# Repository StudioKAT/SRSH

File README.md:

# SRSH

## 概要 / Overview

**SRSH** は、8Stepのシフトレジスタと、8段のサンプル＆ホールド（S&H）を組み合わせたモジュールです。  
- GATE 出力 ×8 を備えた 8Stepシフトレジスタ（DATA / XOR 入力、WRITE / DELETE ボタン付き）  
- シフトレジスタのビットの動きに連動して電圧を受け渡す8段の S&H  
- 8 つのビットを 1 本の CV にまとめる R2R 出力  
の3つを1台にまとめ、リズムとランダムな電圧を同時に作り出せます。  
S&H の入力（SOURCE）に何も挿さなければ、内蔵のホワイトノイズをサンプルします。

---

**SRSH** is a module that combines an 8-step shift register with an 8-stage sample & hold (S&H).  
- An 8-step shift register with 8 GATE outputs (with DATA / XOR inputs and WRITE / DELETE buttons)  
- An 8-stage S&H that passes voltages along in step with the movement of the shift register bits  
- An R2R output that combines the 8 bits into a single CV  

All three are combined in one module, so you can create rhythms and random voltages at the same time.  
When nothing is patched into the S&H input (SOURCE), the module samples its built-in white noise.

## 仕様 / Spec
- Format: Eurorack
- Function: 
- Current needs: +12V: 90mA, -12V: 40mA
- Width: 8 HP
- Depth: 27mm (including power connector)

## 販売 / Sales

StudioKATオフィシャルショップで販売しています。(日本国内限定)  
https://www.studiokat.jp/164466540

## ライセンス / License

この作品は [Creative Commons 表示 - 継承 4.0 国際 (CC BY-SA 4.0)](https://creativecommons.org/licenses/by-sa/4.0/deed.ja) の下でライセンスされています。  
This work is licensed under the [Creative Commons Attribution-ShareAlike 4.0 International License](https://creativecommons.org/licenses/by-sa/4.0/).

## クレジット / Credits

- Designed by : StudioKAT
- Website : https://www.studiokat.jp/
- GitHub : https://github.com/StudioKAT
- X(Twitter) : https://x.com/StudioKAT_synth
- Instagram : https://www.instagram.com/studiokat_modular/

## 更新履歴 / Changelog

- `2026-10-30` v1.0 Released version 1.0

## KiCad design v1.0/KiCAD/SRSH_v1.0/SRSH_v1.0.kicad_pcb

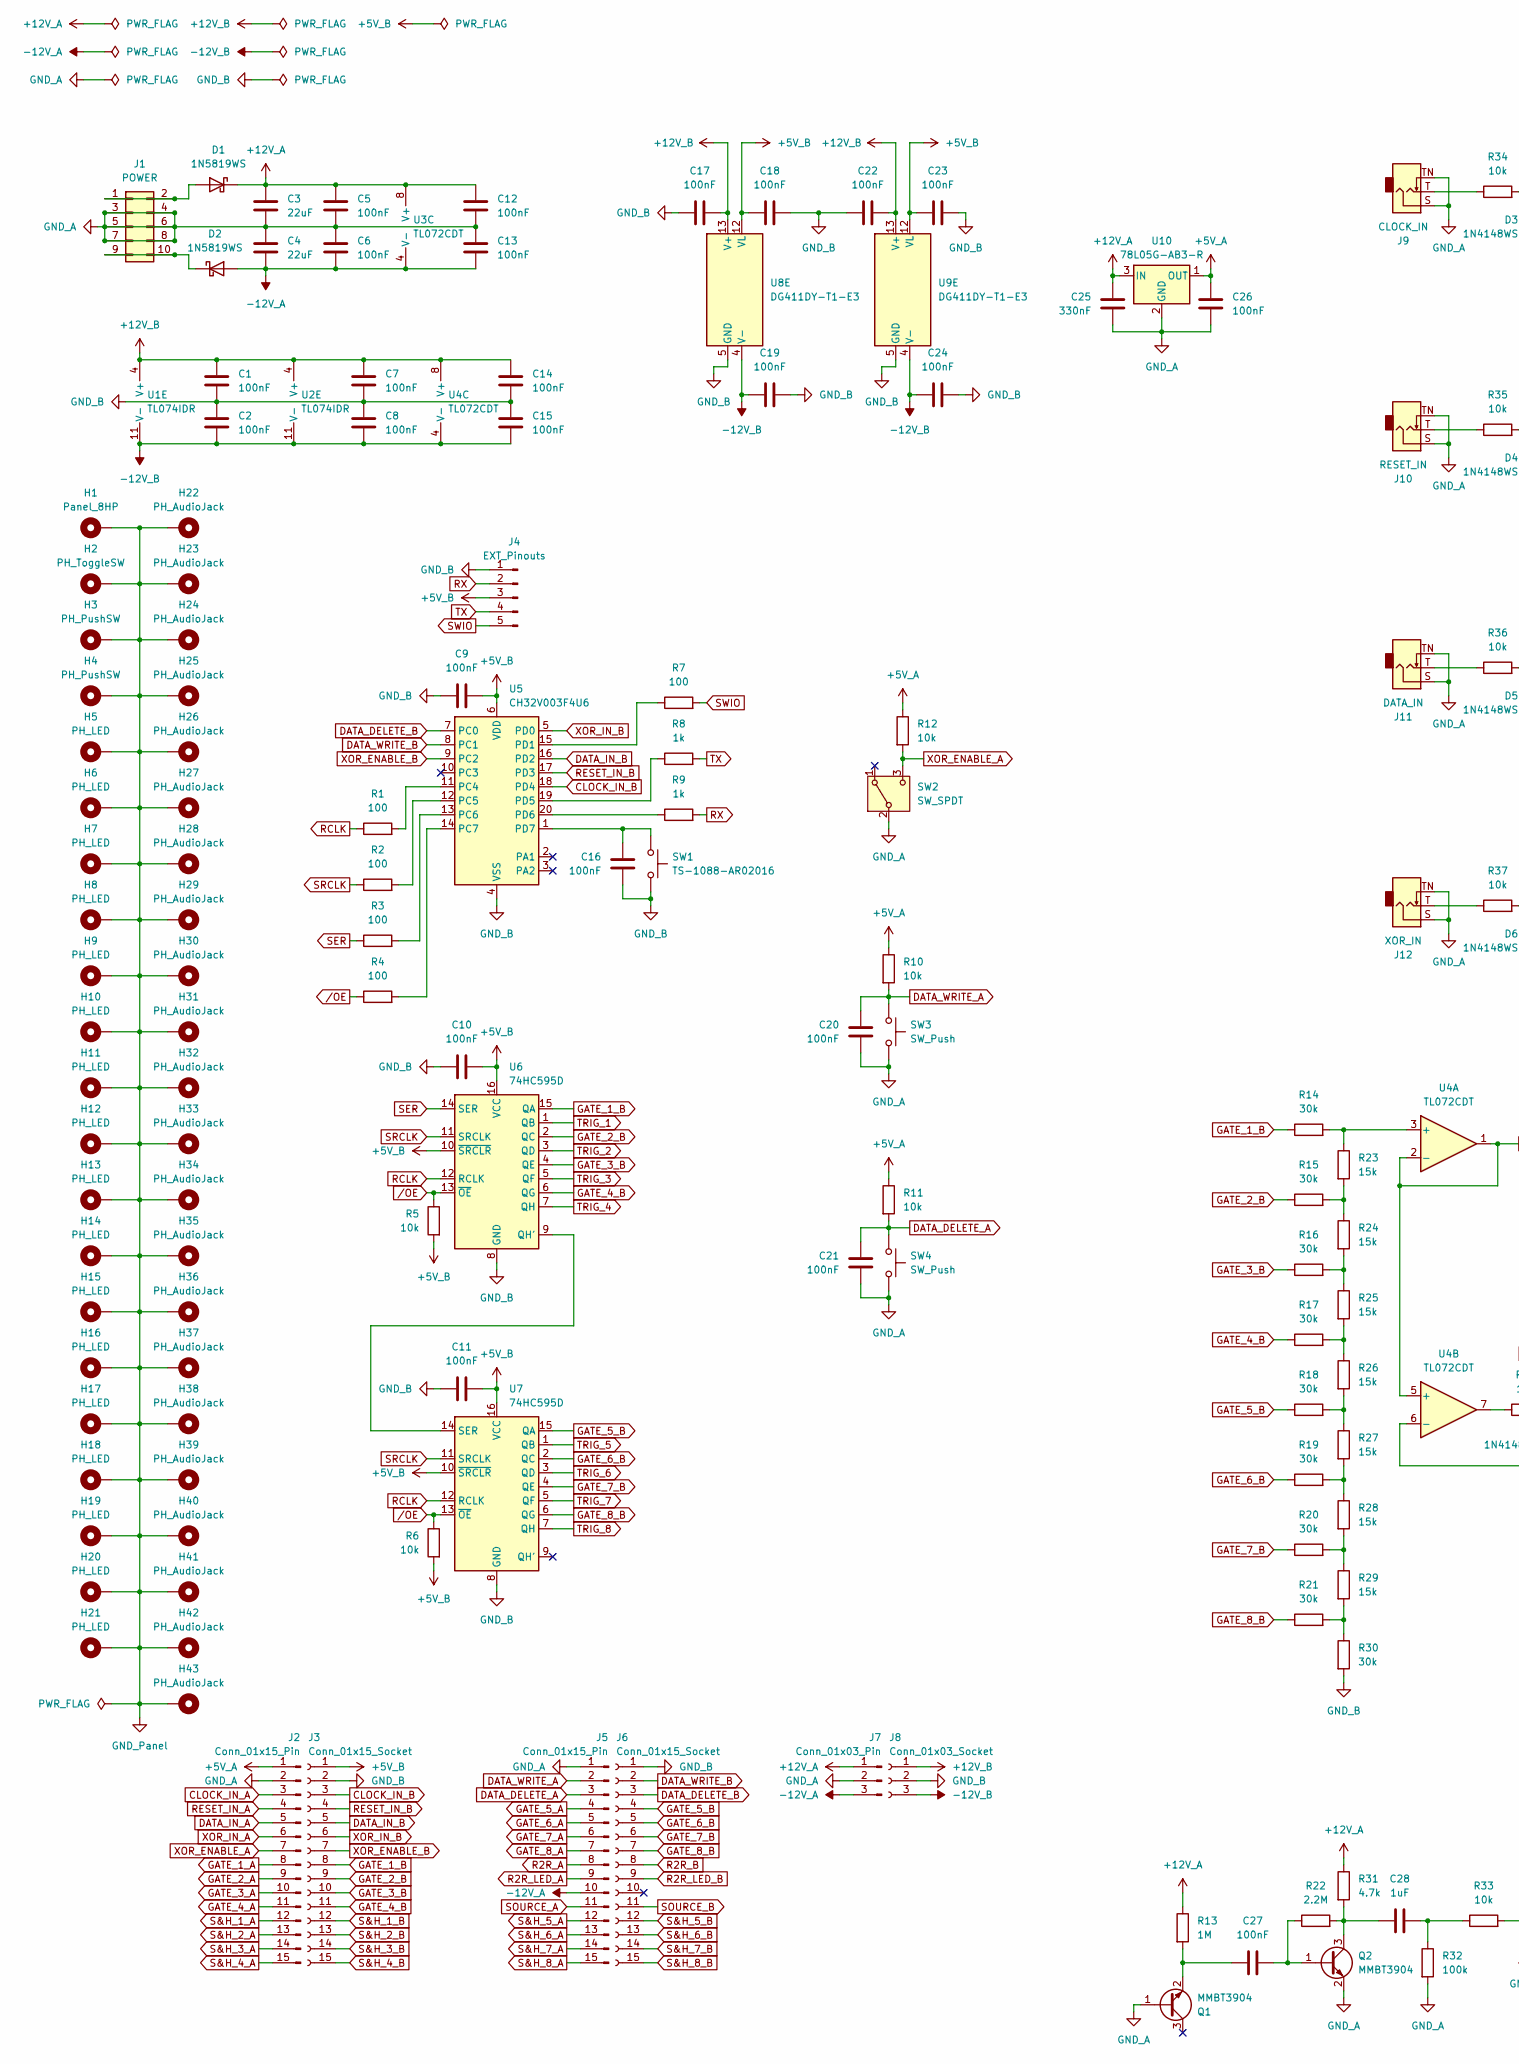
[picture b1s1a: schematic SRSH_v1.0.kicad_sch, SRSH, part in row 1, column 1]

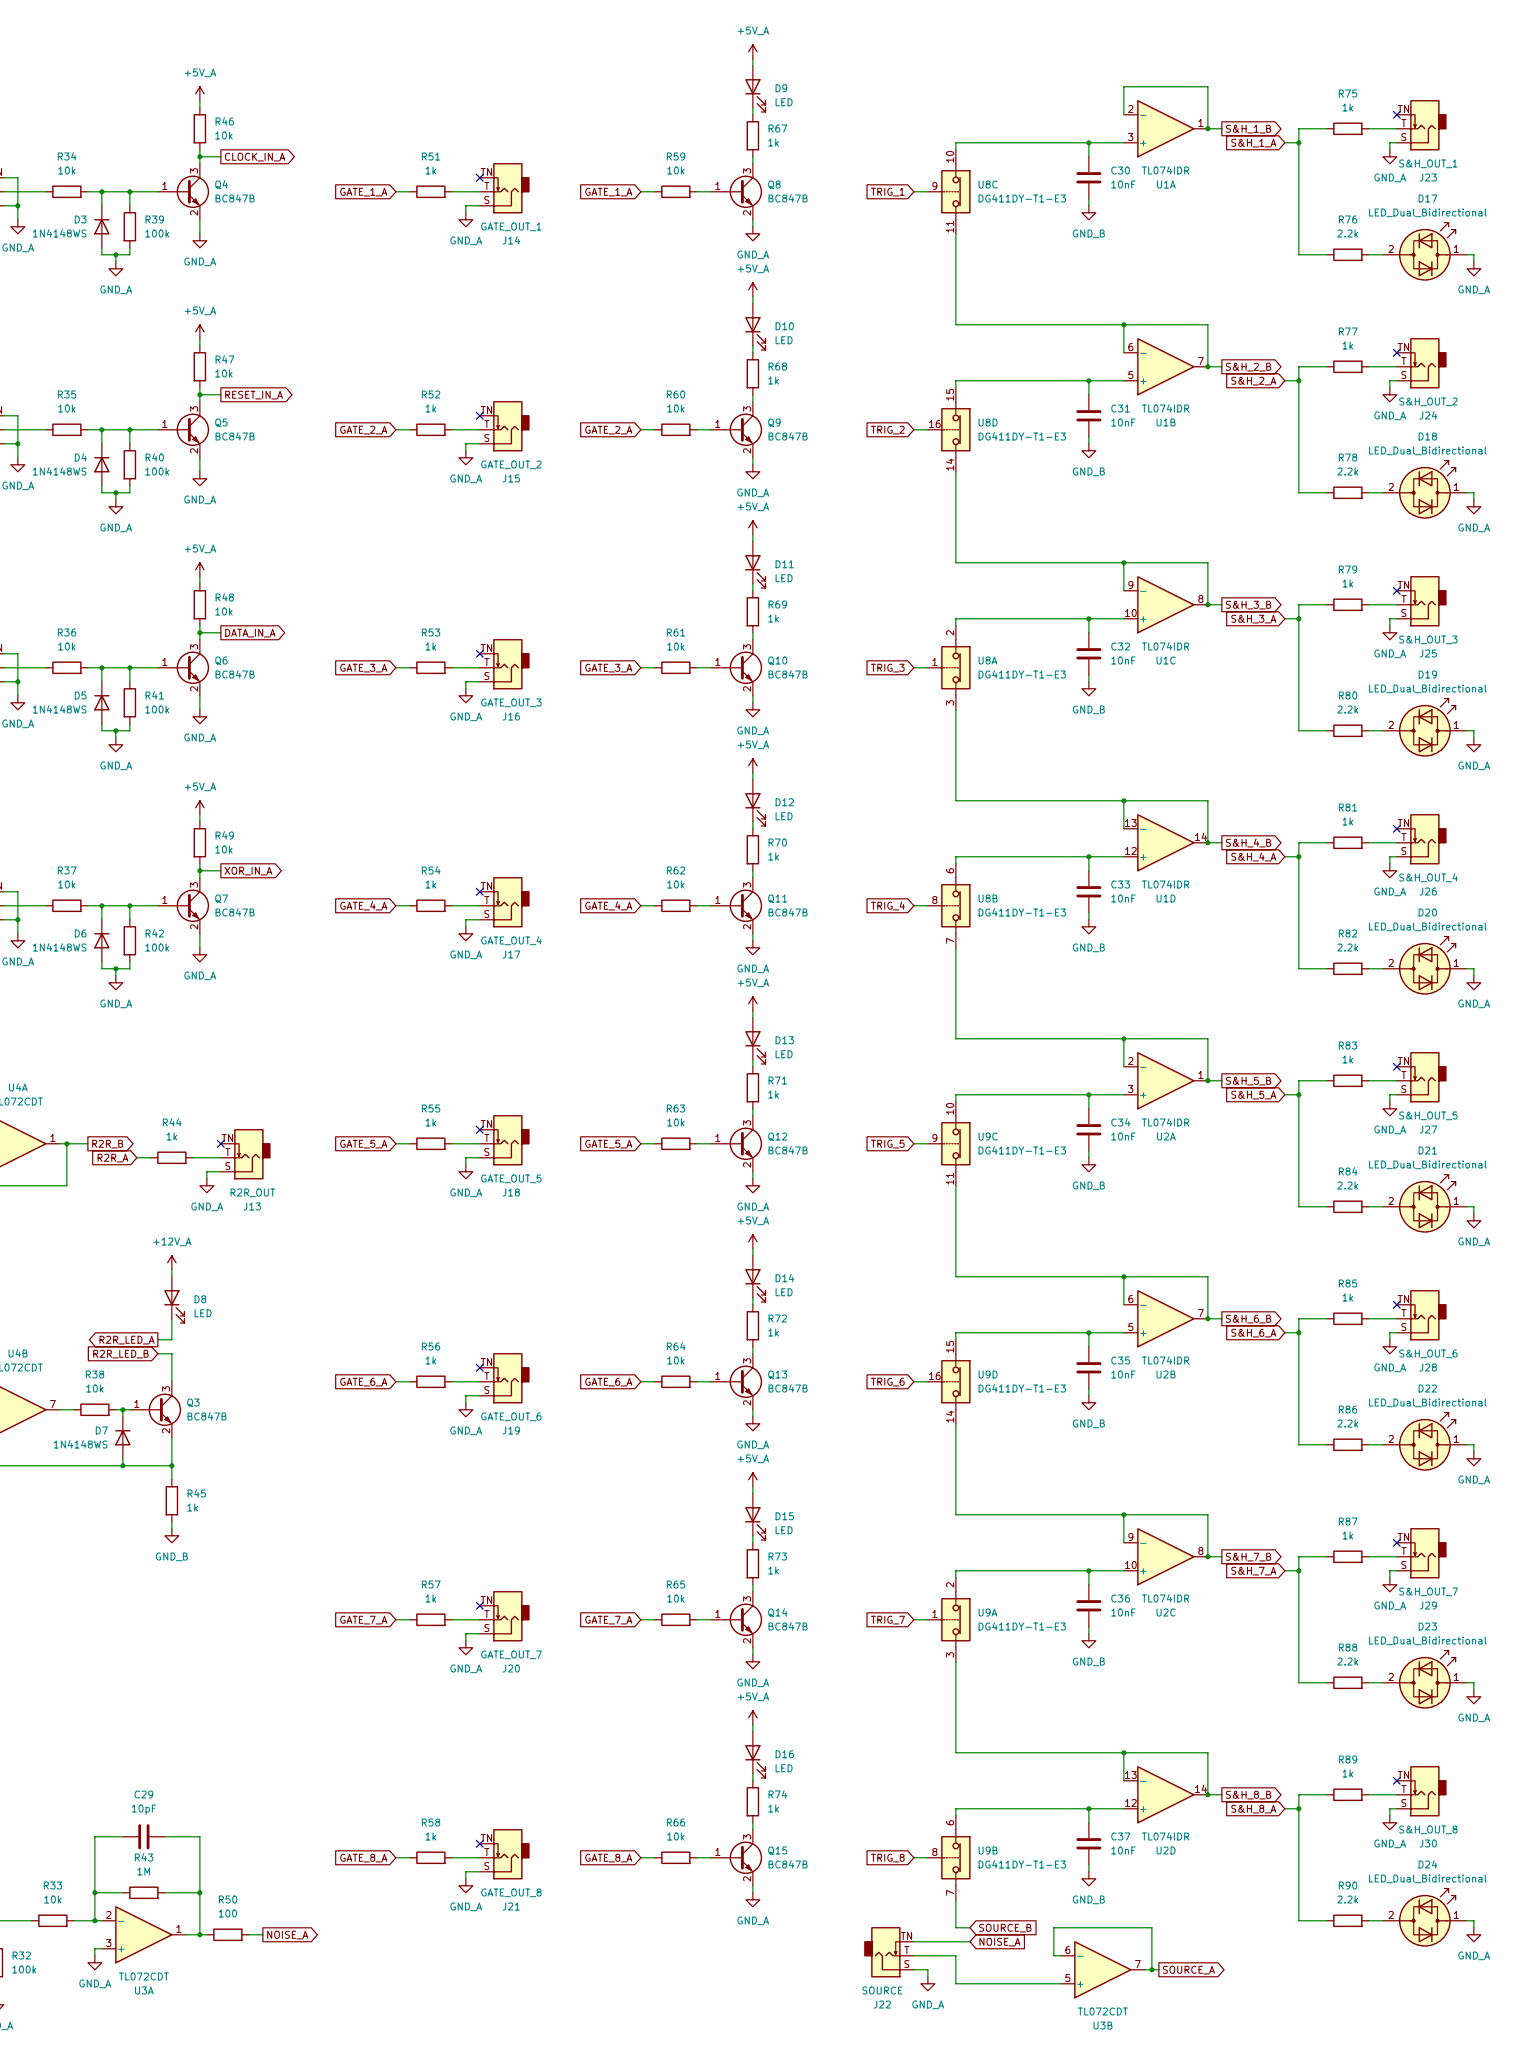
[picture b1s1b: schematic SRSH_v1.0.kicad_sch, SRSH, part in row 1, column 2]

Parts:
C1, C2, C5, C6, C7, C8, C9, C10, C11, C12, C13, C14, C15, C16, C17, C18, C19, C20, C21, C22, C23, C24, C26, C27: 100nF; C_0603_1608Metric; Voltage 50V; Tolerance ±10%; MFR Part CC0603KRX7R9BB104; JLC Type Basic
C3, C4: 22uF; C_0805_2012Metric; Voltage 25V; Tolerance ±20%; MFR Part CL21A226MAQNNNE; JLC Type Basic
C25: 330nF; C_0603_1608Metric; Voltage 25V; Tolerance ±10%; MFR Part 0603B334K250NT; LCSC C1615
C28: 1uF; C_0603_1608Metric; Voltage 50V; Tolerance ±10%; MFR Part CL10A105KB8NNNC; JLC Type Basic
C29: 10pF; C_0603_1608Metric; Voltage 50V; Tolerance ±5%; MFR Part CL10C100JB8NNNC; JLC Type Basic
C30, C31, C32, C33, C34, C35, C36, C37: 10nF; C_0603_1608Metric; Voltage 50V; Tolerance ±10%; MFR Part 0603B103K500NT; JLC Type Basic
D1, D2: 1N5819WS; D_SOD-323; MFR Part 1N5819WS; JLC Type Basic
D3, D4, D5, D6, D7: 1N4148WS; D_SOD-323; MFR Part 1N4148WS; JLC Type Basic
D8, D9, D10, D11, D12, D13, D14, D15, D16: LED; LED_D3.0mm_2hp
D17, D18, D19, D20, D21, D22, D23, D24: LED_Dual_Bidirectional; LED_D3.0mm_2hp
H1: Panel_8HP
H2: PH_ToggleSW; PH_ToggleSwitch_5.1mm_Pad
H3, H4: PH_PushSW; PH_TactileSwitch_5.5mm_Pad
H5, H6, H7, H8, H9, H10, H11, H12, H13, H14, H15, H16, H17, H18, H19, H20, H21: PH_LED; PH_LED_3.0mm_Pad
H22, H23, H24, H25, H26, H27, H28, H29, H30, H31, H32, H33, H34, H35, H36, H37, H38, H39, H40, H41, H42, H43: PH_AudioJack; PH_AudioJack_3.5mm_Pad
J1: POWER; BoxHeader_2x05_2.54mm_Europower
J2, J5: Conn_01x15_Pin; PinHeader_1x15_P2.54mm_Vertical
J3, J6: Conn_01x15_Socket; PinSocket_1x15_P2.54mm_Vertical
J4: EXT_Pinouts; PinHeader_1x05_P2.54mm_Vertical
J7: Conn_01x03_Pin; PinHeader_1x03_P2.54mm_Vertical
J8: Conn_01x03_Socket; PinSocket_1x03_P2.54mm_Vertical
J9: CLOCK_IN; AudioJack_PJ301M-12
J10: RESET_IN; AudioJack_PJ301M-12
J11: DATA_IN; AudioJack_PJ301M-12
J12: XOR_IN; AudioJack_PJ301M-12
J13: R2R_OUT; AudioJack_PJ301M-12
J14: GATE_OUT_1; AudioJack_PJ301M-12
J15: GATE_OUT_2; AudioJack_PJ301M-12
J16: GATE_OUT_3; AudioJack_PJ301M-12
J17: GATE_OUT_4; AudioJack_PJ301M-12
J18: GATE_OUT_5; AudioJack_PJ301M-12
J19: GATE_OUT_6; AudioJack_PJ301M-12
J20: GATE_OUT_7; AudioJack_PJ301M-12
J21: GATE_OUT_8; AudioJack_PJ301M-12
J22: SOURCE; AudioJack_PJ301M-12
J23: S&H_OUT_1; AudioJack_PJ301M-12
J24: S&H_OUT_2; AudioJack_PJ301M-12
J25: S&H_OUT_3; AudioJack_PJ301M-12
J26: S&H_OUT_4; AudioJack_PJ301M-12
J27: S&H_OUT_5; AudioJack_PJ301M-12
J28: S&H_OUT_6; AudioJack_PJ301M-12
J29: S&H_OUT_7; AudioJack_PJ301M-12
J30: S&H_OUT_8; AudioJack_PJ301M-12
Q1, Q2: MMBT3904; SOT-23; MFR Part MMBT3904(RANGE:100-300); JLC Type Basic
Q3, Q4, Q5, Q6, Q7, Q8, Q9, Q10, Q11, Q12, Q13, Q14, Q15: BC847B; SOT-23; MFR Part BC847B; LCSC C20069135
R1, R2, R3, R4, R7, R50: 100; R_0603_1608Metric; Tolerance ±1%; MFR Part 0603WAF1000T5E; JLC Type Basic
R5, R6, R10, R11, R12, R33, R34, R35, R36, R37, R38, R46, R47, R48, R49, R59, R60, R61, R62, R63, R64, R65, R66: 10k; R_0603_1608Metric; Tolerance ±1%; MFR Part 0603WAF1002T5E; JLC Type Basic
R8, R9, R44, R45, R51, R52, R53, R54, R55, R56, R57, R58, R67, R68, R69, R70, R71, R72, R73, R74, R75, R77, R79, R81, R83, R85, R87, R89: 1k; R_0603_1608Metric; Tolerance ±1%; MFR Part 0603WAF1001T5E; JLC Type Basic
R13, R43: 1M; R_0603_1608Metric; Tolerance ±1%; MFR Part 0603WAF1004T5E; JLC Type Basic
R14, R15, R16, R17, R18, R19, R20, R21, R30: 30k; R_0603_1608Metric; Tolerance ±1%; MFR Part 0603WAF3002T5E; JLC Type Basic
R22: 2.2M; R_0603_1608Metric; Tolerance ±1%; MFR Part 0603WAF2204T5E; LCSC C22938
R23, R24, R25, R26, R27, R28, R29: 15k; R_0603_1608Metric; Tolerance ±1%; MFR Part 0603WAF1502T5E; JLC Type Basic
R31: 4.7k; R_0603_1608Metric; Tolerance ±1%; MFR Part 0603WAF4701T5E; JLC Type Basic
R32, R39, R40, R41, R42: 100k; R_0603_1608Metric; Tolerance ±1%; MFR Part 0603WAF1003T5E; JLC Type Basic
R76, R78, R80, R82, R84, R86, R88, R90: 2.2k; R_0603_1608Metric; Tolerance ±1%; MFR Part 0603WAF2201T5E; JLC Type Basic
SW1: TS-1088-AR02016; SW_Push_TS-1088-AR02016; MFR Part TS-1088-AR02016; JLC Type Basic
SW2: SW_SPDT; ToggleSwitch_2MS1-T2-B4-M2-Q-E-S
SW3, SW4: SW_Push; SW_PUSH_6mm_H13mm
U1, U2: TL074IDR; SOIC-14_3.9x8.7mm_P1.27mm; LCSC C6964
U3, U4: TL072CDT; SOIC-8_3.9x4.9mm_P1.27mm; MFR Part TL072CDT; JLC Type Basic
U5: CH32V003F4U6; QFN-20-1EP_3x3mm_P0.4mm_EP1.65x1.65mm; LCSC C5299908
U6, U7: 74HC595D; SOIC-16_3.9x9.9mm_P1.27mm; MFR Part 74HC595D,118; JLC Type Basic
U8, U9: DG411DY-T1-E3; SOIC-16_3.9x9.9mm_P1.27mm; LCSC C17218
U10: 78L05G-AB3-R; SOT-89-3; MFR Part 78L05G-AB3-R; JLC Type Basic

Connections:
+5V_A: C26.1, D9.2 (A), D10.2 (A), D11.2 (A), D12.2 (A), D13.2 (A), D14.2 (A), D15.2 (A), D16.2 (A), J2.1, R10.1, R11.1, R12.1, R46.1, R47.1, R48.1, R49.1, U10.1 (OUT)
+5V_B: C9.2, C10.2, C11.2, C18.1, C23.1, J3.1, J4.3, R5.2, R6.2, U5.6 (VDD), U6.10 (~SRCLR), U6.16 (VCC), U7.10 (~SRCLR), U7.16 (VCC), U8.12 (VL), U9.12 (VL)
+12V_A: C3.1, C5.1, C12.1, C25.1, D1.1 (K), D8.2 (A), J7.1, R13.1, R31.1, U3.8 (V+), U10.3 (IN)
+12V_B: C1.1, C7.1, C14.1, C17.2, C22.2, J8.1, U1.4 (V+), U2.4 (V+), U4.8 (V+), U8.13 (V+), U9.13 (V+)
-12V_A: C4.2, C6.2, C13.2, D2.2 (A), J5.10, J7.3, U3.4 (V-)
-12V_B: C2.2, C8.2, C15.2, C19.1, C24.1, J8.3, U1.11 (V-), U2.11 (V-), U4.4 (V-), U8.4 (V-), U9.4 (V-)
CLOCK_IN_A: J2.3, Q4.3 (C), R46.2
CLOCK_IN_B: J3.3, U5.18 (PD4)
DATA_DELETE_A: C21.1, J5.3, R11.2, SW4.1
DATA_DELETE_B: J6.3, U5.7 (PC0)
DATA_IN_A: J2.5, Q6.3 (C), R48.2
DATA_IN_B: J3.5, U5.16 (PD2)
DATA_WRITE_A: C20.1, J5.2, R10.2, SW3.1
DATA_WRITE_B: J6.2, U5.8 (PC1)
GATE_1_A: J2.8, R51.1, R59.1
GATE_1_B: J3.8, R14.1, U6.15 (QA)
GATE_2_A: J2.9, R52.1, R60.1
GATE_2_B: J3.9, R15.1, U6.2 (QC)
GATE_3_A: J2.10, R53.1, R61.1
GATE_3_B: J3.10, R16.1, U6.4 (QE)
GATE_4_A: J2.11, R54.1, R62.1
GATE_4_B: J3.11, R17.1, U6.6 (QG)
GATE_5_A: J5.4, R55.1, R63.1
GATE_5_B: J6.4, R18.1, U7.15 (QA)
GATE_6_A: J5.5, R56.1, R64.1
GATE_6_B: J6.5, R19.1, U7.2 (QC)
GATE_7_A: J5.6, R57.1, R65.1
GATE_7_B: J6.6, R20.1, U7.4 (QE)
GATE_8_A: J5.7, R58.1, R66.1
GATE_8_B: J6.7, R21.1, U7.6 (QG)
GND_A: C3.2, C4.1, C5.2, C6.1, C12.2, C13.1, C20.2, C21.2, C25.2, C26.2, D3.2 (A), D4.2 (A), D5.2 (A), D6.2 (A), D17.1 (KA), D18.1 (KA), D19.1 (KA), D20.1 (KA), D21.1 (KA), D22.1 (KA), D23.1 (KA), D24.1 (KA), J1.3, J1.4, J1.5, J1.6, J1.7, J1.8, J2.2, J5.1, J7.2, J9.S, J9.TN, J10.S, J10.TN, J11.S, J11.TN, J12.S, J12.TN, J13.S, J14.S, J15.S, J16.S, J17.S, J18.S, J19.S, J20.S, J21.S, J22.S, J23.S, J24.S, J25.S, J26.S, J27.S, J28.S, J29.S, J30.S, Q1.1 (B), Q2.2 (E), Q4.2 (E), Q5.2 (E), Q6.2 (E), Q7.2 (E), Q8.2 (E), Q9.2 (E), Q10.2 (E), Q11.2 (E), Q12.2 (E), Q13.2 (E), Q14.2 (E), Q15.2 (E), R32.2, R39.2, R40.2, R41.2, R42.2, SW2.2 (B), SW3.2, SW4.2, U3.3 (+), U10.2 (GND)
GND_B: C1.2, C2.1, C7.2, C8.1, C9.1, C10.1, C11.1, C14.2, C15.1, C16.2, C17.1, C18.2, C19.2, C22.1, C23.2, C24.2, C30.2, C31.2, C32.2, C33.2, C34.2, C35.2, C36.2, C37.2, J3.2, J4.1, J6.1, J8.2, R30.2, R45.2, SW1.2, U5.4 (VSS), U5.21 (VSS), U6.8 (GND), U7.8 (GND), U8.5 (GND), U9.5 (GND)
GND_Panel: H1.1 (1_1), H2.1 (1_1), H3.1 (1_1), H4.1 (1_1), H5.1 (1_1), H6.1 (1_1), H7.1 (1_1), H8.1 (1_1), H9.1 (1_1), H10.1 (1_1), H11.1 (1_1), H12.1 (1_1), H13.1 (1_1), H14.1 (1_1), H15.1 (1_1), H16.1 (1_1), H17.1 (1_1), H18.1 (1_1), H19.1 (1_1), H20.1 (1_1), H21.1 (1_1), H22.1 (1_1), H23.1 (1_1), H24.1 (1_1), H25.1 (1_1), H26.1 (1_1), H27.1 (1_1), H28.1 (1_1), H29.1 (1_1), H30.1 (1_1), H31.1 (1_1), H32.1 (1_1), H33.1 (1_1), H34.1 (1_1), H35.1 (1_1), H36.1 (1_1), H37.1 (1_1), H38.1 (1_1), H39.1 (1_1), H40.1 (1_1), H41.1 (1_1), H42.1 (1_1), H43.1 (1_1)
NOISE_A: J22.TN, R50.2
unnamed: C28.2, R32.1, R33.1
unnamed: C29.2, R43.2, R50.1, U3.1
unnamed: D1.2 (A), J1.1, J1.2
unnamed: D2.1 (K), J1.9, J1.10
unnamed: D3.1 (K), Q4.1 (B), R34.2, R39.1
unnamed: D4.1 (K), Q5.1 (B), R35.2, R40.1
unnamed: D5.1 (K), Q6.1 (B), R36.2, R41.1
unnamed: D6.1 (K), Q7.1 (B), R37.2, R42.1
unnamed: D7.2 (A), Q3.2 (E), R45.1, U4.6 (-)
unnamed: D7.1 (K), Q3.1 (B), R38.2
unnamed: D9.1 (K), R67.1
unnamed: D10.1 (K), R68.1
unnamed: D11.1 (K), R69.1
unnamed: D12.1 (K), R70.1
unnamed: D13.1 (K), R71.1
unnamed: D14.1 (K), R72.1
unnamed: D15.1 (K), R73.1
unnamed: D16.1 (K), R74.1
unnamed: D17.2 (AK), R76.2
unnamed: D18.2 (AK), R78.2
unnamed: D19.2 (AK), R80.2
unnamed: D20.2 (AK), R82.2
unnamed: D21.2 (AK), R84.2
unnamed: D22.2 (AK), R86.2
unnamed: D23.2 (AK), R88.2
unnamed: D24.2 (AK), R90.2
unnamed: J9.T, R34.1
unnamed: J10.T, R35.1
unnamed: J11.T, R36.1
unnamed: J12.T, R37.1
unnamed: J13.T, R44.2
unnamed: J14.T, R51.2
unnamed: J15.T, R52.2
unnamed: J16.T, R53.2
unnamed: J17.T, R54.2
unnamed: J18.T, R55.2
unnamed: J19.T, R56.2
unnamed: J20.T, R57.2
unnamed: J21.T, R58.2
unnamed: J23.T, R75.2
unnamed: J24.T, R77.2
unnamed: J25.T, R79.2
unnamed: J26.T, R81.2
unnamed: J27.T, R83.2
unnamed: J28.T, R85.2
unnamed: J29.T, R87.2
unnamed: J30.T, R89.2
unnamed: C27.1, Q1.2 (E), R13.2
unnamed: C27.2, Q2.1 (B), R22.1
unnamed: C28.1, Q2.3 (C), R22.2, R31.2
unnamed: Q8.1 (B), R59.2
unnamed: Q8.3 (C), R67.2
unnamed: Q9.1 (B), R60.2
unnamed: Q9.3 (C), R68.2
unnamed: Q10.1 (B), R61.2
unnamed: Q10.3 (C), R69.2
unnamed: Q11.1 (B), R62.2
unnamed: Q11.3 (C), R70.2
unnamed: Q12.1 (B), R63.2
unnamed: Q12.3 (C), R71.2
unnamed: Q13.1 (B), R64.2
unnamed: Q13.3 (C), R72.2
unnamed: Q14.1 (B), R65.2
unnamed: Q14.3 (C), R73.2
unnamed: Q15.1 (B), R66.2
unnamed: Q15.3 (C), R74.2
unnamed: R15.2, R23.2, R24.1
unnamed: R16.2, R24.2, R25.1
unnamed: R17.2, R25.2, R26.1
unnamed: R18.2, R26.2, R27.1
unnamed: R19.2, R27.2, R28.1
unnamed: R20.2, R28.2, R29.1
unnamed: R21.2, R29.2, R30.1
unnamed: R38.1, U4.7
unnamed: C30.1, U1.3 (+), U8.10
unnamed: C31.1, U1.5 (+), U8.15
unnamed: C32.1, U1.10 (+), U8.2
unnamed: C33.1, U1.12 (+), U8.6
unnamed: C34.1, U2.3 (+), U9.10
unnamed: C35.1, U2.5 (+), U9.15
unnamed: C36.1, U2.10 (+), U9.2
unnamed: C37.1, U2.12 (+), U9.6
unnamed: C29.1, R33.2, R43.1, U3.2 (-)
unnamed: J22.T, U3.5 (+)
unnamed: R14.2, R23.1, U4.3 (+)
unnamed: R1.2, U5.11 (PC4)
unnamed: R2.2, U5.12 (PC5)
unnamed: R3.2, U5.13 (PC6)
unnamed: R4.2, U5.14 (PC7)
unnamed: R7.1, U5.15 (PD1)
unnamed: R8.1, U5.19 (PD5)
unnamed: R9.1, U5.20 (PD6)
unnamed: C16.1, SW1.1, U5.1 (PD7)
unnamed: U6.9 (QH'), U7.14 (SER)
R2R_A: J5.8, R44.1
R2R_B: J6.8, U4.1, U4.2 (-), U4.5 (+)
R2R_LED_A: D8.1 (K), J5.9
R2R_LED_B: J6.9, Q3.3 (C)
RCLK: R1.1, U6.12 (RCLK), U7.12 (RCLK)
RESET_IN_A: J2.4, Q5.3 (C), R47.2
RESET_IN_B: J3.4, U5.17 (PD3)
RX: J4.2, R9.2
S&H_1_A: J2.12, R75.1, R76.1
S&H_1_B: J3.12, U1.1, U1.2 (-)
S&H_2_A: J2.13, R77.1, R78.1
S&H_2_B: J3.13, U1.6 (-), U1.7, U8.11
S&H_3_A: J2.14, R79.1, R80.1
S&H_3_B: J3.14, U1.8, U1.9 (-), U8.14
S&H_4_A: J2.15, R81.1, R82.1
S&H_4_B: J3.15, U1.13 (-), U1.14, U8.3
S&H_5_A: J5.12, R83.1, R84.1
S&H_5_B: J6.12, U2.1, U2.2 (-), U8.7
S&H_6_A: J5.13, R85.1, R86.1
S&H_6_B: J6.13, U2.6 (-), U2.7, U9.11
S&H_7_A: J5.14, R87.1, R88.1
S&H_7_B: J6.14, U2.8, U2.9 (-), U9.14
S&H_8_A: J5.15, R89.1, R90.1
S&H_8_B: J6.15, U2.13 (-), U2.14, U9.3
SER: R3.1, U6.14 (SER)
SOURCE_A: J5.11, U3.6 (-), U3.7
SOURCE_B: J6.11, U9.7
SRCLK: R2.1, U6.11 (SRCLK), U7.11 (SRCLK)
SWIO: J4.5, R7.2
TRIG_1: U6.1 (QB), U8.9
TRIG_2: U6.3 (QD), U8.16
TRIG_3: U6.5 (QF), U8.1
TRIG_4: U6.7 (QH), U8.8
TRIG_5: U7.1 (QB), U9.9
TRIG_6: U7.3 (QD), U9.16
TRIG_7: U7.5 (QF), U9.1
TRIG_8: U7.7 (QH), U9.8
TX: J4.4, R8.2
XOR_ENABLE_A: J2.7, R12.2, SW2.3 (C)
XOR_ENABLE_B: J3.7, U5.9 (PC2)
XOR_IN_A: J2.6, Q7.3 (C), R49.2
XOR_IN_B: J3.6, U5.5 (PD0)
/OE: R4.1, R5.1, R6.1, U6.13 (~OE), U7.13 (~OE)

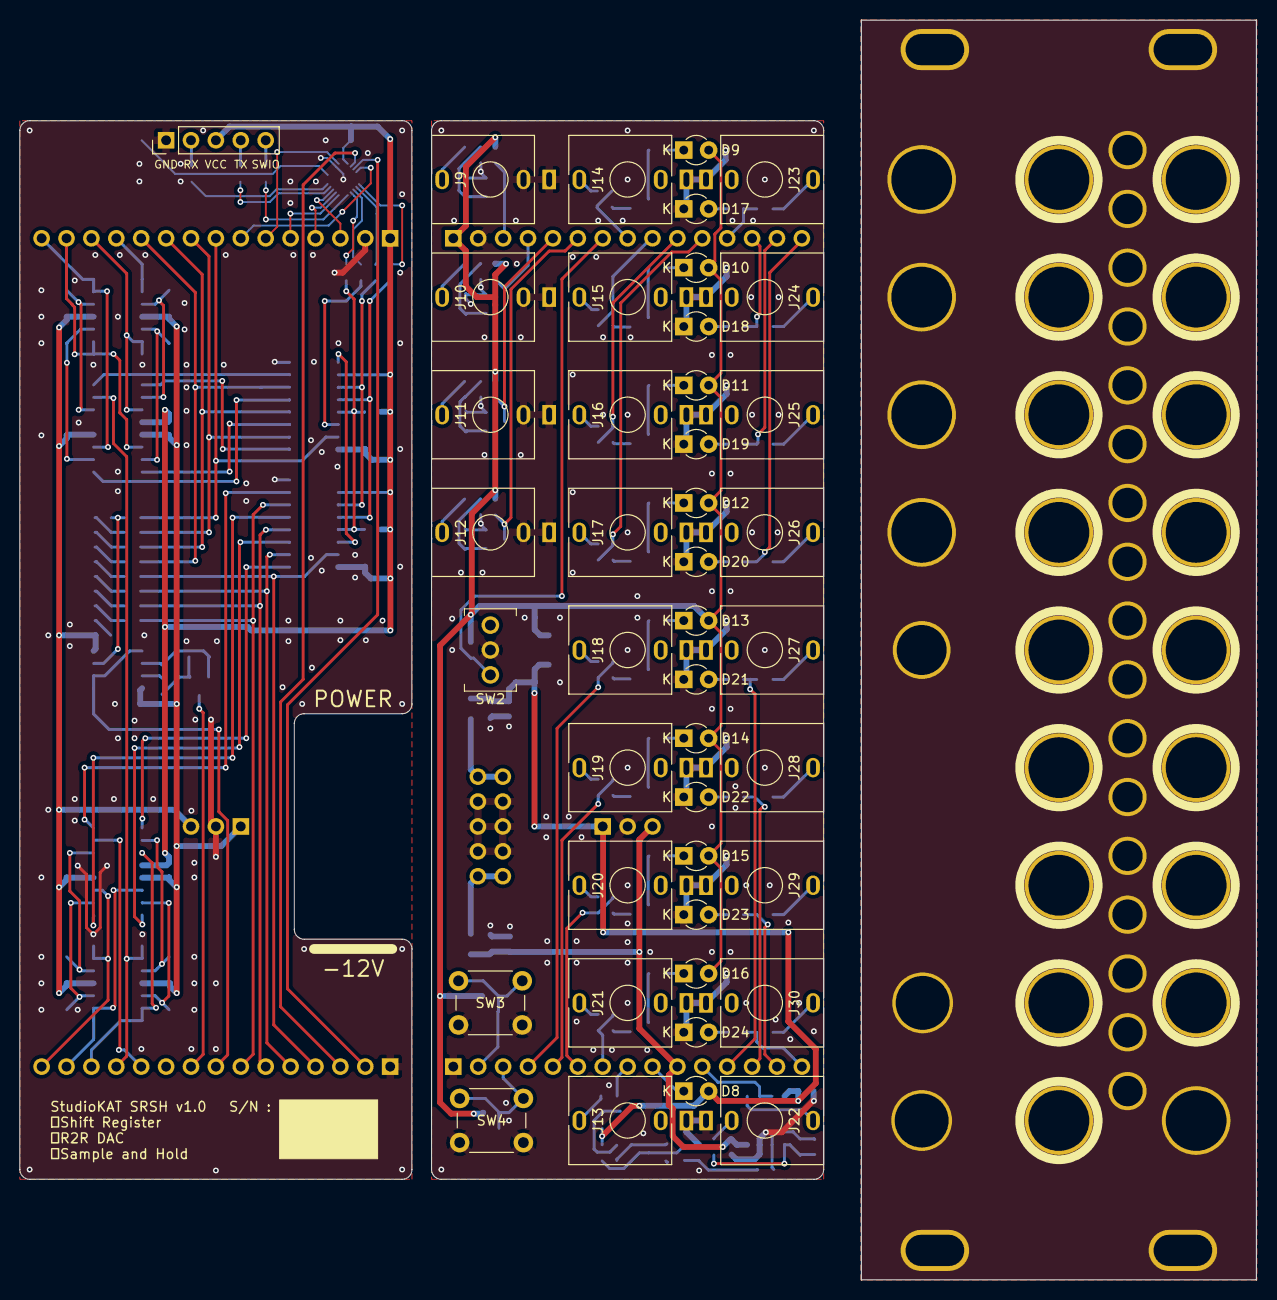
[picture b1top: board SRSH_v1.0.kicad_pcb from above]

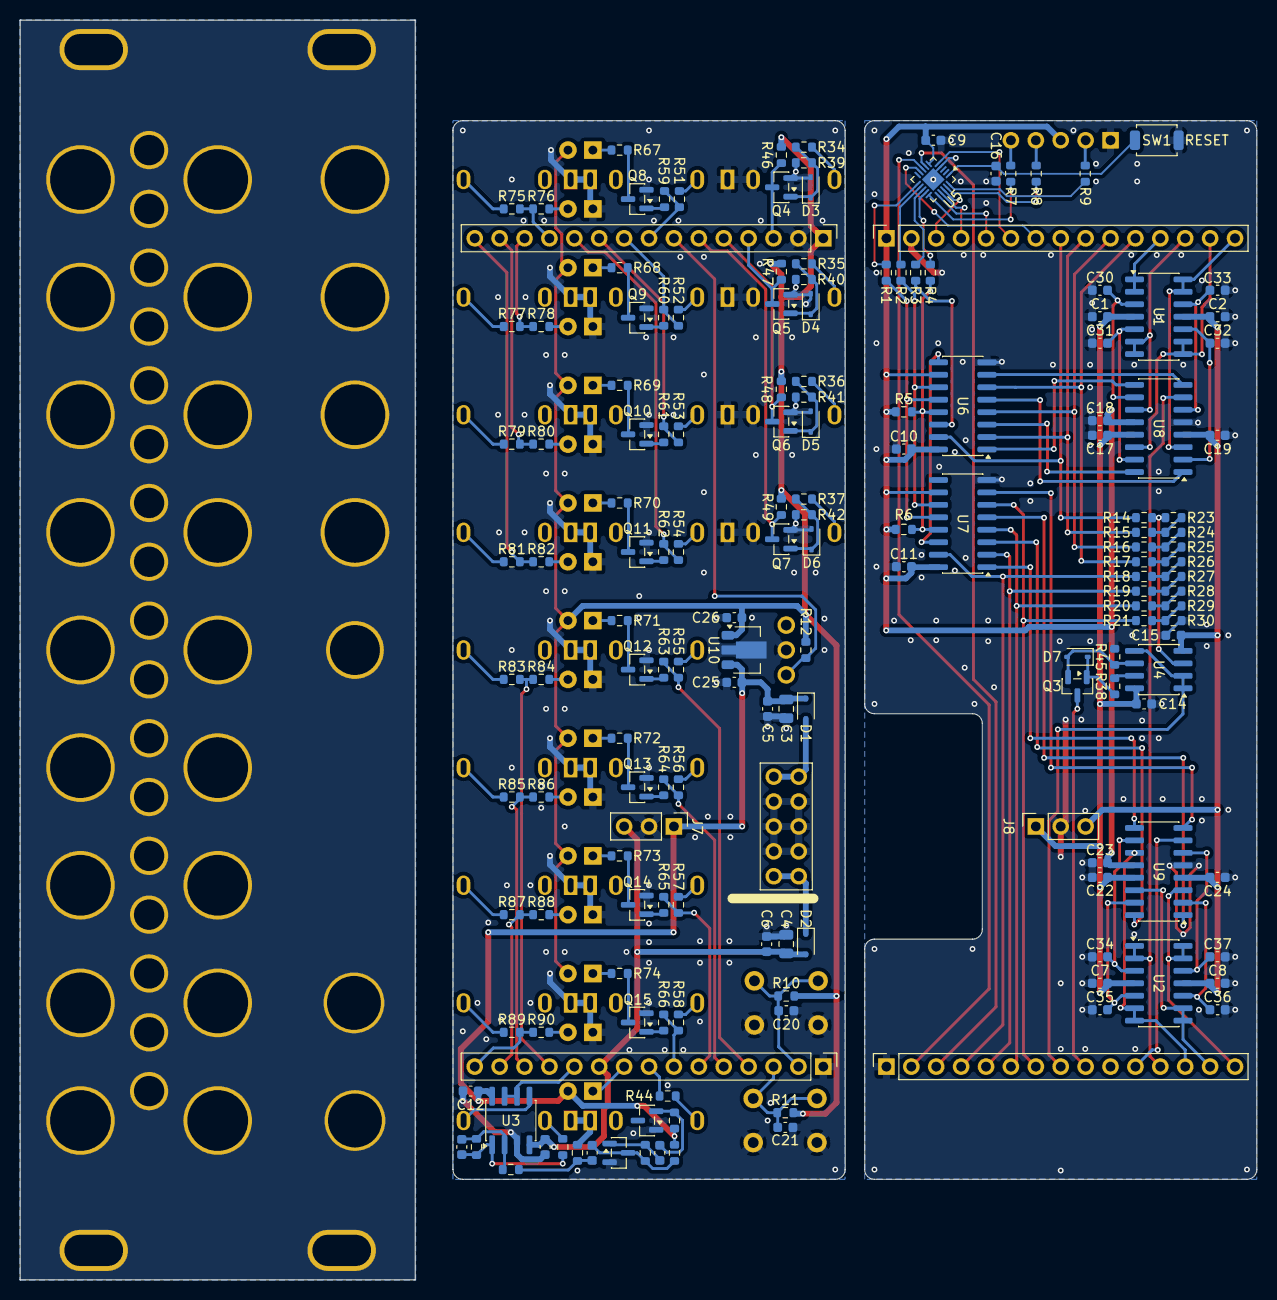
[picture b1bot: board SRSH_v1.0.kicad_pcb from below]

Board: 2 copper layers, 126.2 x 128.5 mm, 253 parts (167 on the bottom side), 171 nets.
